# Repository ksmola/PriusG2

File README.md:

# Prius G2 Inverter controller

## About 

Inverter control board for Toyota Prius Gen 2 (XW20) inverter. 
Some of the schematics are based on Johannes Huebner's work found [here](https://github.com/jsphuebner/inverter-hardware).
Running [openinverter](http://www.openinverter.org) firmware.

    - ESP32 on board
    - AMPSEAL connectors
    - 3D printed enclosure

## Prerequisites 

ESP32 needs [ported webinterface](https://github.com/Bedz01/esp32-web-interface-port)
Get latest openinverter firmware [here](https://github.com/jsphuebner/stm32-sine/releases)

## Pinout 

Pinout is documented on the bottom silk of the PCB

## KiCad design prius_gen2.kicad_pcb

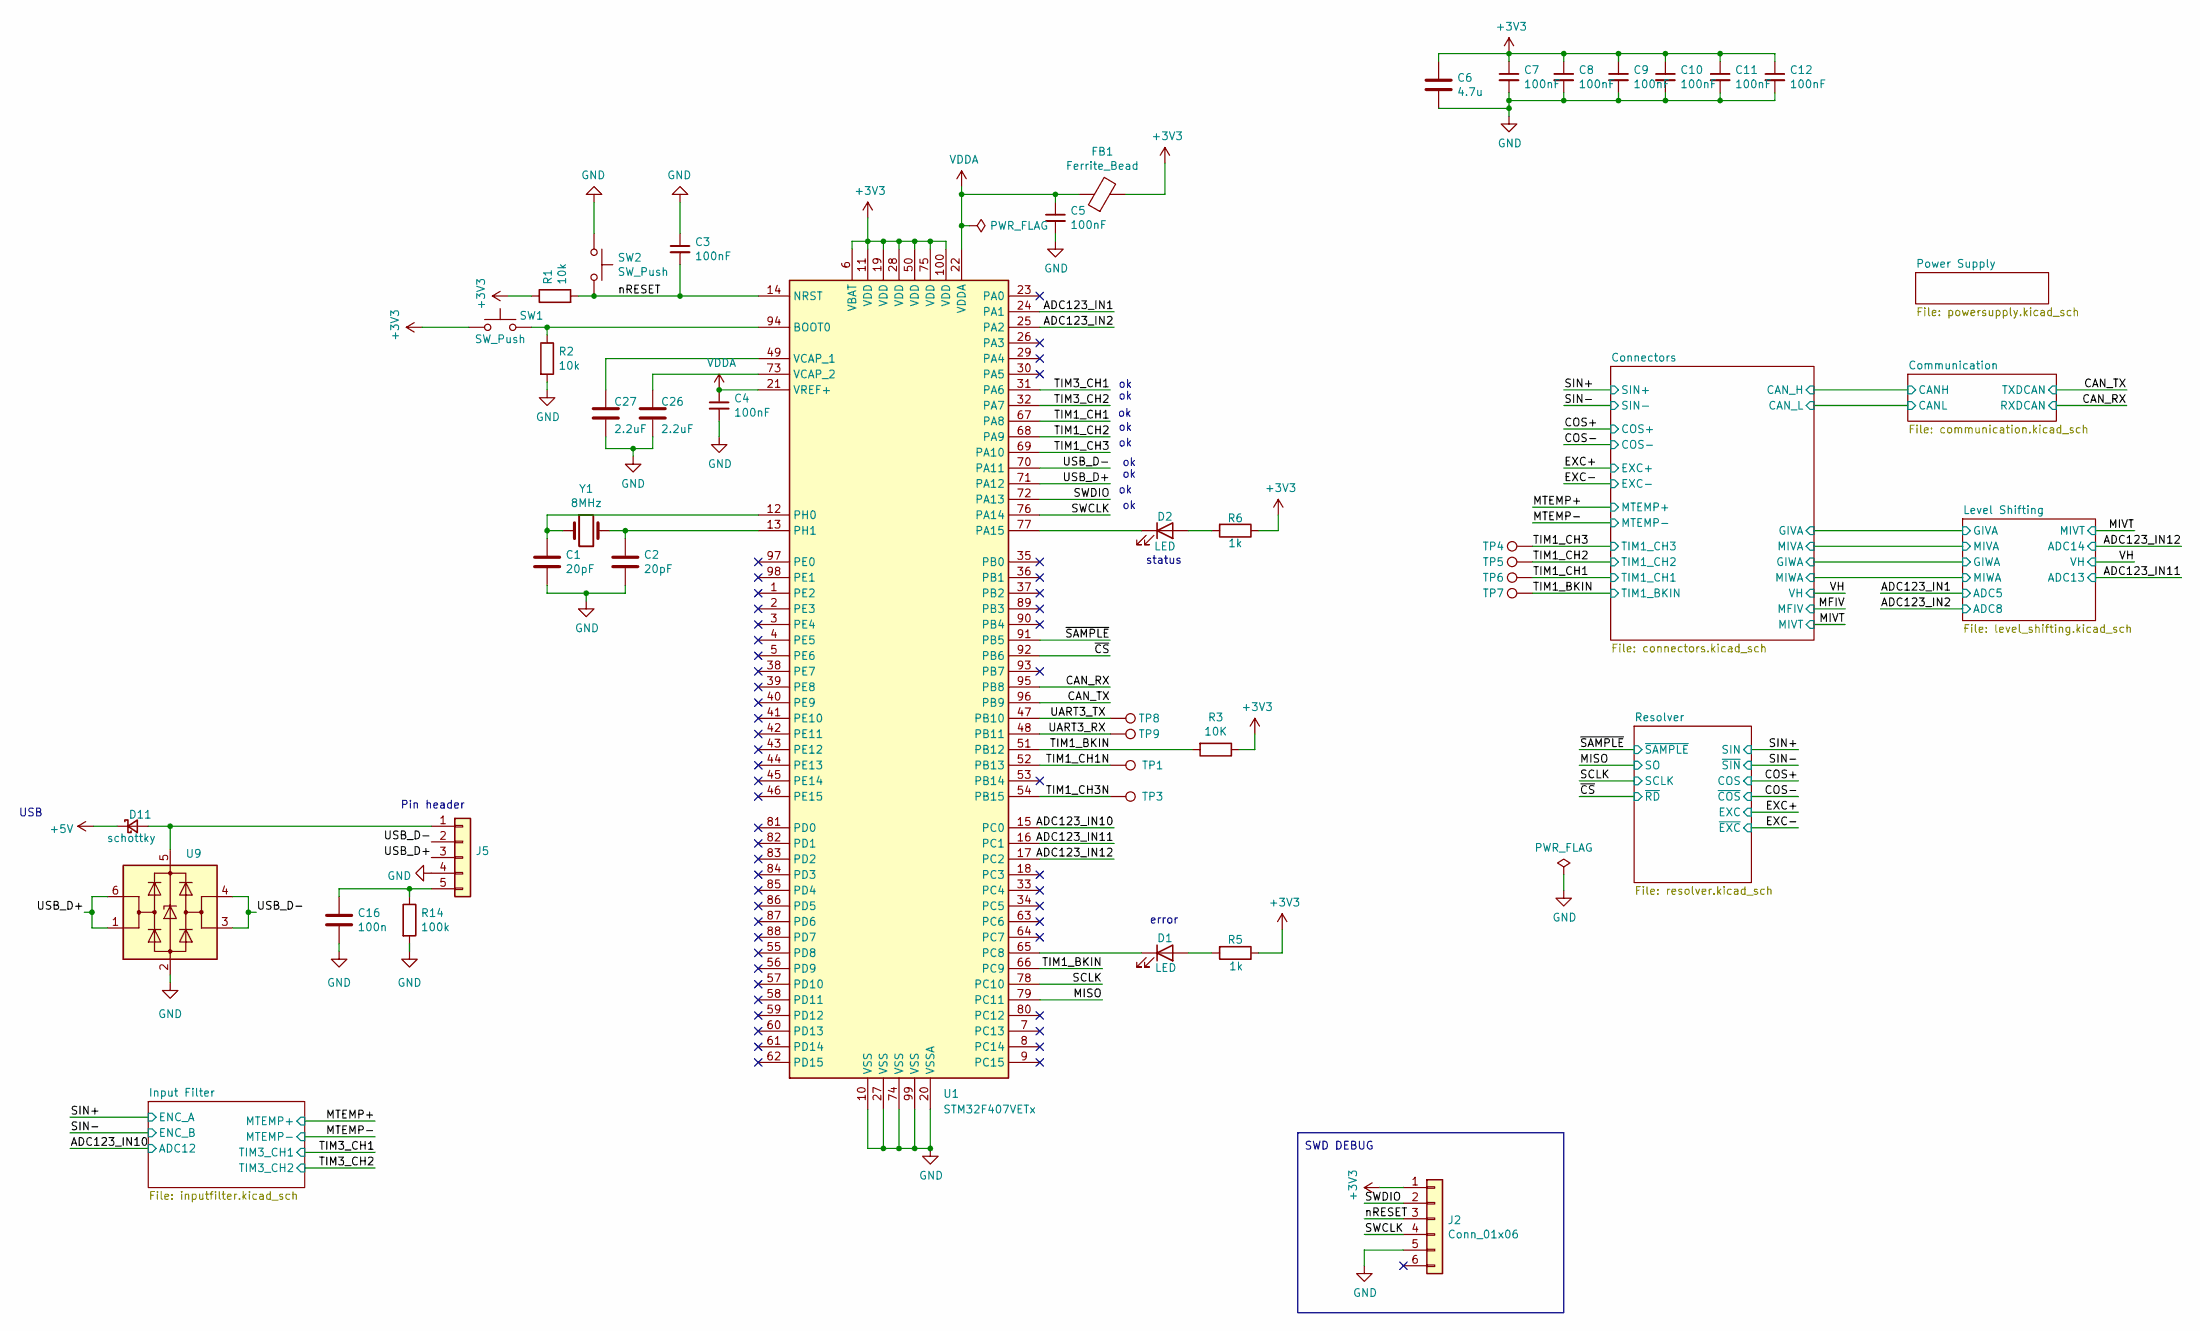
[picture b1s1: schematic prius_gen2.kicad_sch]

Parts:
C1, C2: 20pF; C_0603_1608Metric; mpn CC0603JRNPO9BN200; LCSC C105621
C3, C4, C5, C7, C8, C9, C10, C11, C12: 100nF; C_0603_1608Metric
C6: 4.7u; C_0603_1608Metric
C16: 100n; C_0603_1608Metric; LCSC C14663
C26, C27: 2.2uF; C_0603_1608Metric; LCSC C23630
D1, D2: LED; LED_0603_1608Metric_Castellated
D11: schottky; D_SOD-123; LCSC C8598
FB1: Ferrite_Bead; C_0805_2012Metric
J2: Conn_01x06; Tag-Connect_TC2030-IDC-NL_2x03_P1.27mm_Vertical
J5: PinSocket_1x05_P2.54mm_Vertical; LCSC N/A
R1, R2: 10k; R_0603_1608Metric; LCSC C25804
R3: 10K; R_0603_1608Metric; LCSC C25804
R5, R6: 1k; R_0603_1608Metric
R14: 100k; R_0402_1005Metric; LCSC C25741
SW1, SW2: SW_Push; SW_SPST_EVQQ2
TP1, TP3, TP4, TP5, TP6, TP7, TP8, TP9: TestPoint; TestPoint_Keystone_5000-5004_Miniature; LCSC C238124
U1: STM32F407VETx; LQFP-100_14x14mm_P0.5mm
U9: SOT-23-6; LCSC C7519
Y1: 8MHz; Crystal_SMD_5032-2Pin_5.0x3.2mm; LCSC C115962

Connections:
+3V3: C6.1, C7.1, C8.1, C9.1, C10.1, C11.1, C12.1, FB1.2, J2.1, R1.1, R3.1, R5.1, R6.1, SW1.1, U1.6 (VBAT), U1.11 (VDD), U1.19 (VDD), U1.28 (VDD), U1.50 (VDD), U1.75 (VDD), U1.100 (VDD); also elsewhere on the board
+5V: D11.1 (K); also elsewhere on the board
/ADC123_IN1: U1.24 (PA1); also elsewhere on the board
/ADC123_IN2: U1.25 (PA2); also elsewhere on the board
/ADC123_IN10: U1.15 (PC0); also elsewhere on the board
/ADC123_IN11: U1.16 (PC1); also elsewhere on the board
/ADC123_IN12: U1.17 (PC2); also elsewhere on the board
/CAN_RX: U1.95 (PB8); also elsewhere on the board
/CAN_TX: U1.96 (PB9); also elsewhere on the board
/MISO: U1.79 (PC11); also elsewhere on the board
/SCLK: U1.78 (PC10); also elsewhere on the board
/SWCLK: J2.4, U1.76 (PA14)
/SWDIO: J2.2, U1.72 (PA13)
/TIM1_BKIN: R3.2, TP7.1, U1.51 (PB12), U1.66 (PC9); also elsewhere on the board
/TIM1_CH1: TP6.1, U1.67 (PA8); also elsewhere on the board
/TIM1_CH1N: TP1.1, U1.52 (PB13)
/TIM1_CH2: TP5.1, U1.68 (PA9); also elsewhere on the board
/TIM1_CH3: TP4.1, U1.69 (PA10); also elsewhere on the board
/TIM1_CH3N: TP3.1, U1.54 (PB15)
/TIM3_CH1: U1.31 (PA6); also elsewhere on the board
/TIM3_CH2: U1.32 (PA7); also elsewhere on the board
/UART3_RX: TP9.1, U1.48 (PB11)
/UART3_TX: TP8.1, U1.47 (PB10)
/USB_D+: J5.3, U1.71 (PA12), U9.1 (I/O1), U9.6 (I/O1)
/USB_D-: J5.2, U1.70 (PA11), U9.3 (I/O2), U9.4 (I/O2)
/nRESET: C3.2, J2.3, R1.2, SW2.2, U1.14 (NRST)
/~CS: U1.92 (PB6); also elsewhere on the board
/~SAMPLE: U1.91 (PB5); also elsewhere on the board
GND: C1.1, C2.1, C3.1, C4.2, C5.2, C6.2, C7.2, C8.2, C9.2, C10.2, C11.2, C12.2, C16.2, C26.2, C27.2, J2.5, J5.4, R2.2, R14.2, SW2.1, U1.10 (VSS), U1.20 (VSSA), U1.27 (VSS), U1.74 (VSS), U1.99 (VSS), U9.2 (GND); also elsewhere on the board
unnamed: D1.2 (A), R5.2
unnamed: D1.1 (K), U1.65 (PC8)
unnamed: D2.2 (A), R6.2
unnamed: D2.1 (K), U1.77 (PA15)
unnamed: D11.2 (A), J5.1, U9.5 (VBUS)
unnamed: C16.1, J5.5, R14.1
unnamed: R2.1, SW1.2, U1.94 (BOOT0)
unnamed: C1.2, U1.12 (PH0), Y1.1
unnamed: C2.2, U1.13 (PH1), Y1.2
unnamed: C27.1, U1.49 (VCAP_1)
unnamed: C26.1, U1.73 (VCAP_2)
VDDA: C4.1, C5.1, FB1.1, U1.21 (VREF+), U1.22 (VDDA)

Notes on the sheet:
USB
status
SWD DEBUG
Pin header
error

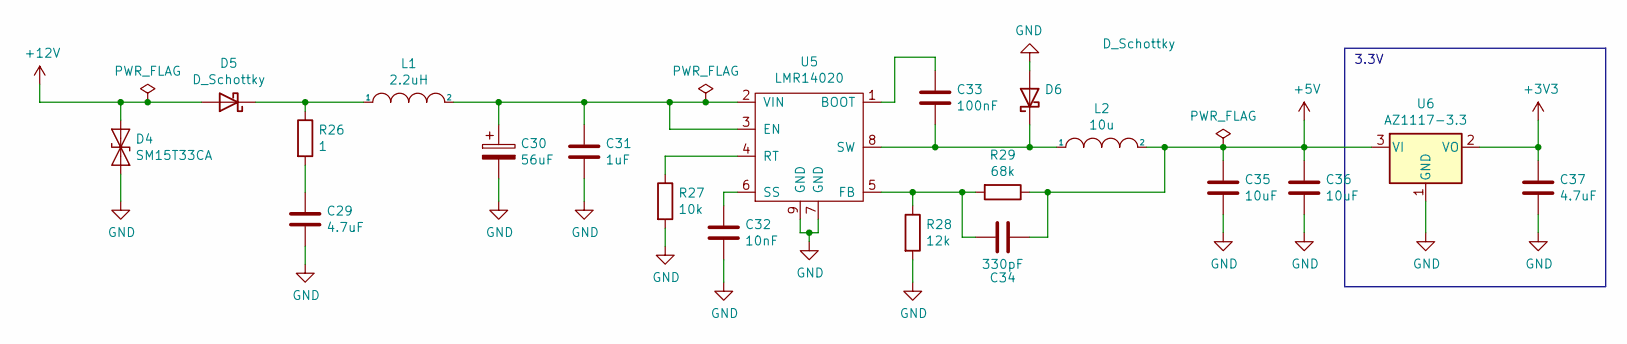
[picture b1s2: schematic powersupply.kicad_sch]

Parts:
C29, C37: 4.7uF; C_0603_1608Metric
C30: 56uF; CP_Radial_D8.0mm_P3.50mm
C31: 1uF; C_0603_1608Metric
C32: 10nF; C_0603_1608Metric; LCSC C302008
C33: 100nF; C_0603_1608Metric
C34: 330pF; C_0603_1608Metric
C35, C36: 10uF; C_0603_1608Metric
D4: SM15T33CA; D_SMC
D5, D6: D_Schottky; D_SMA
L1: 2.2uH; L_1210_3225Metric
L2: 10u; MWSA0503
R26: 1; R_0603_1608Metric
R27: 10k; R_0603_1608Metric; LCSC C25804
R28: 12k; R_0603_1608Metric
R29: 68k; R_0603_1608Metric; LCSC C23231
U5: LMR14020; SOIC-8-1EP_3.9x4.9mm_P1.27mm_EP2.29x3mm
U6: AZ1117-3.3; SOT-223-3_TabPin2

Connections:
+3V3: C37.1, U6.2 (VO); also elsewhere on the board
+5V: C34.2, C35.1, C36.1, L2.2, R29.1, U6.3 (VI); also elsewhere on the board
+12V: D4.1 (A1), D5.2 (A); also elsewhere on the board
GND: C29.2, C30.2, C31.2, C32.2, C35.2, C36.2, C37.2, D4.2 (A2), D6.2 (A), R27.2, R28.2, U5.7 (GND), U5.9 (GND), U6.1 (GND); also elsewhere on the board
unnamed: C29.1, R26.2
unnamed: D5.1 (K), L1.1, R26.1
unnamed: C33.2, D6.1 (K), L2.1, U5.8 (SW)
unnamed: C33.1, U5.1 (BOOT)
unnamed: C30.1, C31.1, L1.2, U5.2 (VIN), U5.3 (EN)
unnamed: C34.1, R28.1, R29.2, U5.5 (FB)
unnamed: R27.1, U5.4 (RT)
unnamed: C32.1, U5.6 (SS)

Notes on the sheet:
3.3V

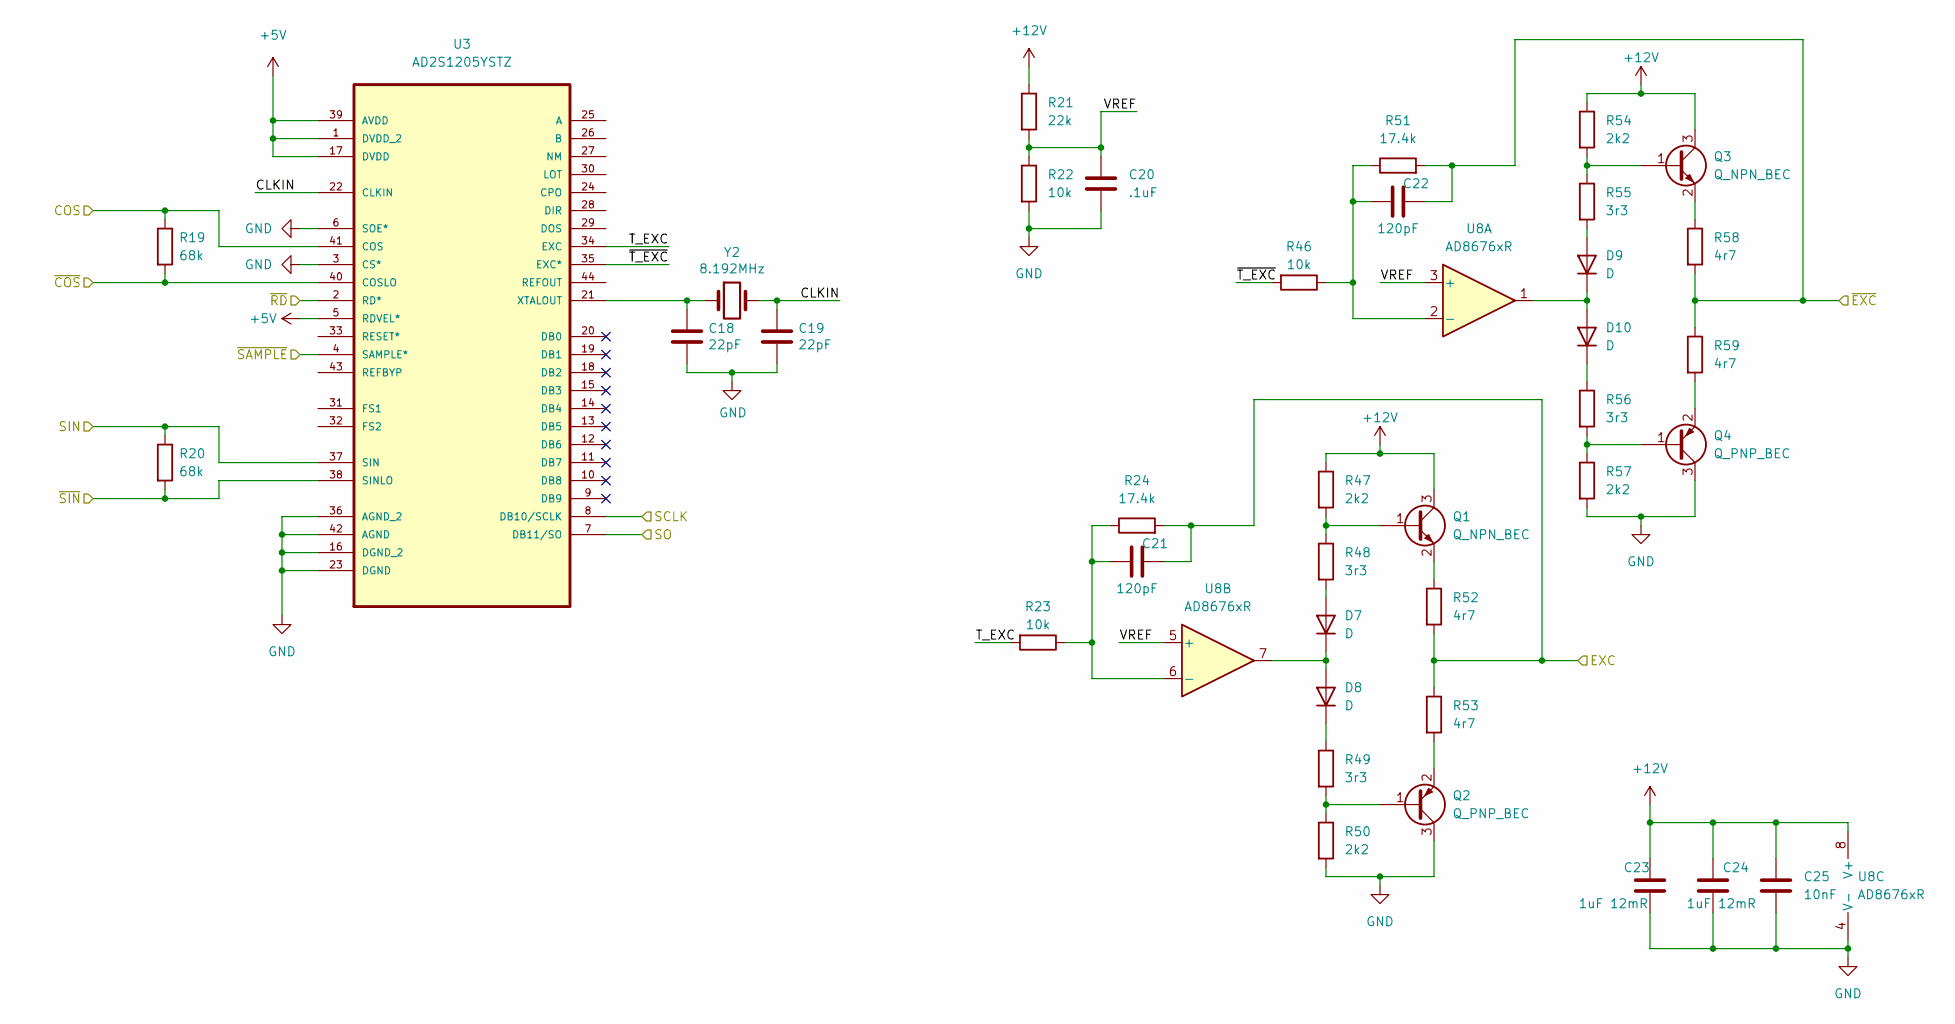
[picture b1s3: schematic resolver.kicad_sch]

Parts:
C18, C19: 22pF; C_0603_1608Metric; mpn CC0603JRNPO9BN200; LCSC C309441
C20: .1uF; C_0603_1608Metric; LCSC C15725
C21, C22: 120pF; C_0603_1608Metric; LCSC C1643
C23, C24: 1uF 12mR; C_0603_1608Metric; LCSC C106858
C25: 10nF; C_0603_1608Metric; LCSC C302008
D7, D8, D9, D10: D; D_SOD-123; LCSC C83528
Q1, Q3: Q_NPN_BEC; TSOT-23; LCSC C2144
Q2, Q4: Q_PNP_BEC; TSOT-23; LCSC C8326
R19, R20: 68k; R_0603_1608Metric; LCSC C23231
R21: 22k; R_0603_1608Metric
R22, R23, R46: 10k; R_0603_1608Metric; LCSC C25804
R24, R51: 17.4k; R_0603_1608Metric; LCSC C269466
R47, R50, R54, R57: 2k2; R_0603_1608Metric; LCSC C325643
R48, R49, R55, R56: 3r3; R_0603_1608Metric; LCSC C365471
R52, R53, R58, R59: 4r7; R_0603_1608Metric; LCSC C23164
U3: AD2S1205YSTZ; QFP80P1200X1200X160-44N; MPN AD2S1205YSTZ; LCSC C91729
U8: AD8676xR; SOIC-8_3.9x4.9mm_P1.27mm; LCSC C28133
Y2: 8.192MHz; Crystal_SMD_5032-2Pin_5.0x3.2mm; LCSC C115962

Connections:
+5V: U3.1 (DVDD_2), U3.5 (RDVEL*), U3.17 (DVDD), U3.39 (AVDD); also elsewhere on the board
+12V: C23.1, C24.1, C25.1, Q1.3 (C), Q3.3 (C), R21.1, R47.1, R54.1, U8.8 (V+); also elsewhere on the board
/COS+: R19.1, U3.41 (COS); also elsewhere on the board
/COS-: R19.2, U3.40 (COSLO); also elsewhere on the board
/EXC+: C21.2, R24.2, R52.2, R53.1; also elsewhere on the board
/EXC-: C22.2, R51.2, R58.2, R59.1; also elsewhere on the board
/MISO: U3.7 (DB11/SO); also elsewhere on the board
/Resolver/CLKIN: C19.2, U3.22 (CLKIN), Y2.2
/Resolver/T_EXC: R23.2, U3.34 (EXC)
/Resolver/VREF: C20.1, R21.2, R22.1, U8.3 (+), U8.5 (+)
/Resolver/~T_EXC: R46.2, U3.35 (EXC*)
/SCLK: U3.8 (DB10/SCLK); also elsewhere on the board
/SIN+: R20.1, U3.37 (SIN); also elsewhere on the board
/SIN-: R20.2, U3.38 (SINLO); also elsewhere on the board
/~CS: U3.2 (RD*); also elsewhere on the board
/~SAMPLE: U3.4 (SAMPLE*); also elsewhere on the board
GND: C18.1, C19.1, C20.2, C23.2, C24.2, C25.2, Q2.3 (C), Q4.3 (C), R22.2, R50.2, R57.2, U3.3 (CS*), U3.6 (SOE*), U3.16 (DGND_2), U3.23 (DGND), U3.36 (AGND_2), U3.42 (AGND), U8.4 (V-); also elsewhere on the board
unnamed: D7.2 (A), R48.2
unnamed: D7.1 (K), D8.2 (A), U8.7
unnamed: D8.1 (K), R49.1
unnamed: D9.2 (A), R55.2
unnamed: D9.1 (K), D10.2 (A), U8.1
unnamed: D10.1 (K), R56.1
unnamed: Q1.1 (B), R47.2, R48.1
unnamed: Q1.2 (E), R52.1
unnamed: Q2.1 (B), R49.2, R50.1
unnamed: Q2.2 (E), R53.2
unnamed: Q3.1 (B), R54.2, R55.1
unnamed: Q3.2 (E), R58.1
unnamed: Q4.1 (B), R56.2, R57.1
unnamed: Q4.2 (E), R59.2
unnamed: C18.2, U3.21 (XTALOUT), Y2.1
unnamed: C22.1, R46.1, R51.1, U8.2 (-)
unnamed: C21.1, R23.1, R24.1, U8.6 (-)

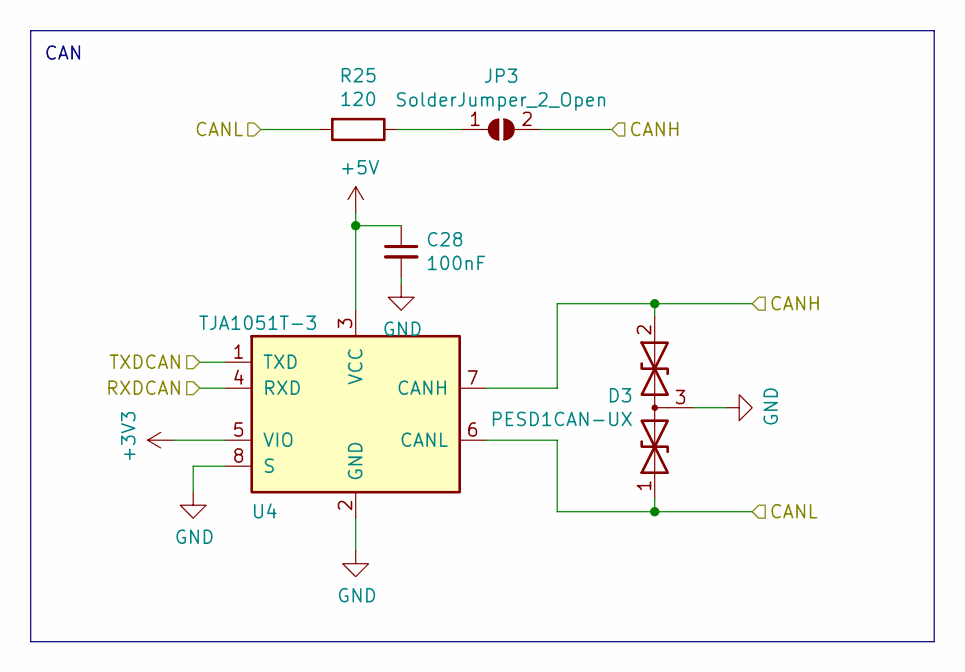
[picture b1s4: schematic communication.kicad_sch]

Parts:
C28: 100nF; C_0603_1608Metric
D3: PESD1CAN-UX; SOT-323_SC-70
JP3: SolderJumper_2_Open; SolderJumper-2_P1.3mm_Open_TrianglePad1.0x1.5mm
R25: 120; R_0603_1608Metric
U4: TJA1051T-3; SOIC-8_3.9x4.9mm_P1.27mm

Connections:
+3V3: U4.5 (VIO); also elsewhere on the board
+5V: C28.1, U4.3 (VCC); also elsewhere on the board
/CAN_RX: U4.4 (RXD); also elsewhere on the board
/CAN_TX: U4.1 (TXD); also elsewhere on the board
/Communication/CANH: D3.2 (A2), JP3.2 (B), U4.7 (CANH); also elsewhere on the board
/Communication/CANL: D3.1 (A1), R25.2, U4.6 (CANL); also elsewhere on the board
GND: C28.2, D3.3 (common), U4.2 (GND), U4.8 (S); also elsewhere on the board
unnamed: JP3.1 (A), R25.1

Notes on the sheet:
CAN

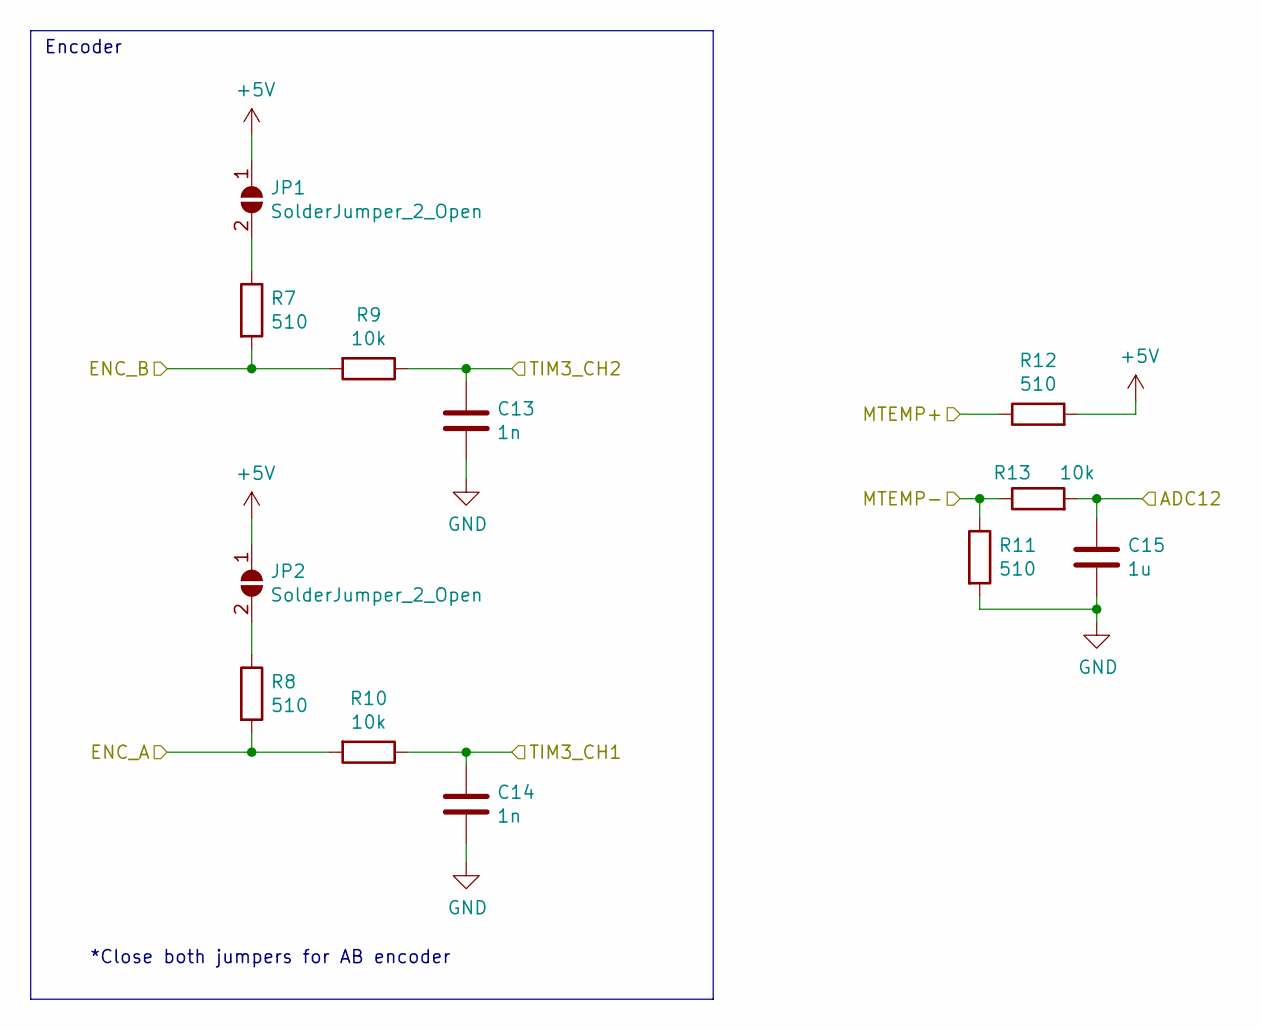
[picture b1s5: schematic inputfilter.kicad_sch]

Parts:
C13, C14: 1n; C_0603_1608Metric
C15: 1u; C_0603_1608Metric
JP1, JP2: SolderJumper_2_Open; SolderJumper-2_P1.3mm_Open_TrianglePad1.0x1.5mm
R7, R8, R11, R12: 510; R_0603_1608Metric
R9, R10, R13: 10k; R_0603_1608Metric; LCSC C25804

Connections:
+5V: JP1.1 (A), JP2.1 (A), R12.2; also elsewhere on the board
/ADC123_IN10: C15.1, R13.2; also elsewhere on the board
/MTEMP+: R12.1; also elsewhere on the board
/MTEMP-: R11.1, R13.1; also elsewhere on the board
/SIN+: R8.2, R10.2; also elsewhere on the board
/SIN-: R7.2, R9.2; also elsewhere on the board
/TIM3_CH1: C14.1, R10.1; also elsewhere on the board
/TIM3_CH2: C13.1, R9.1; also elsewhere on the board
GND: C13.2, C14.2, C15.2, R11.2; also elsewhere on the board
unnamed: JP1.2 (B), R7.1
unnamed: JP2.2 (B), R8.1

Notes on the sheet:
*Close both jumpers for AB encoder
Encoder

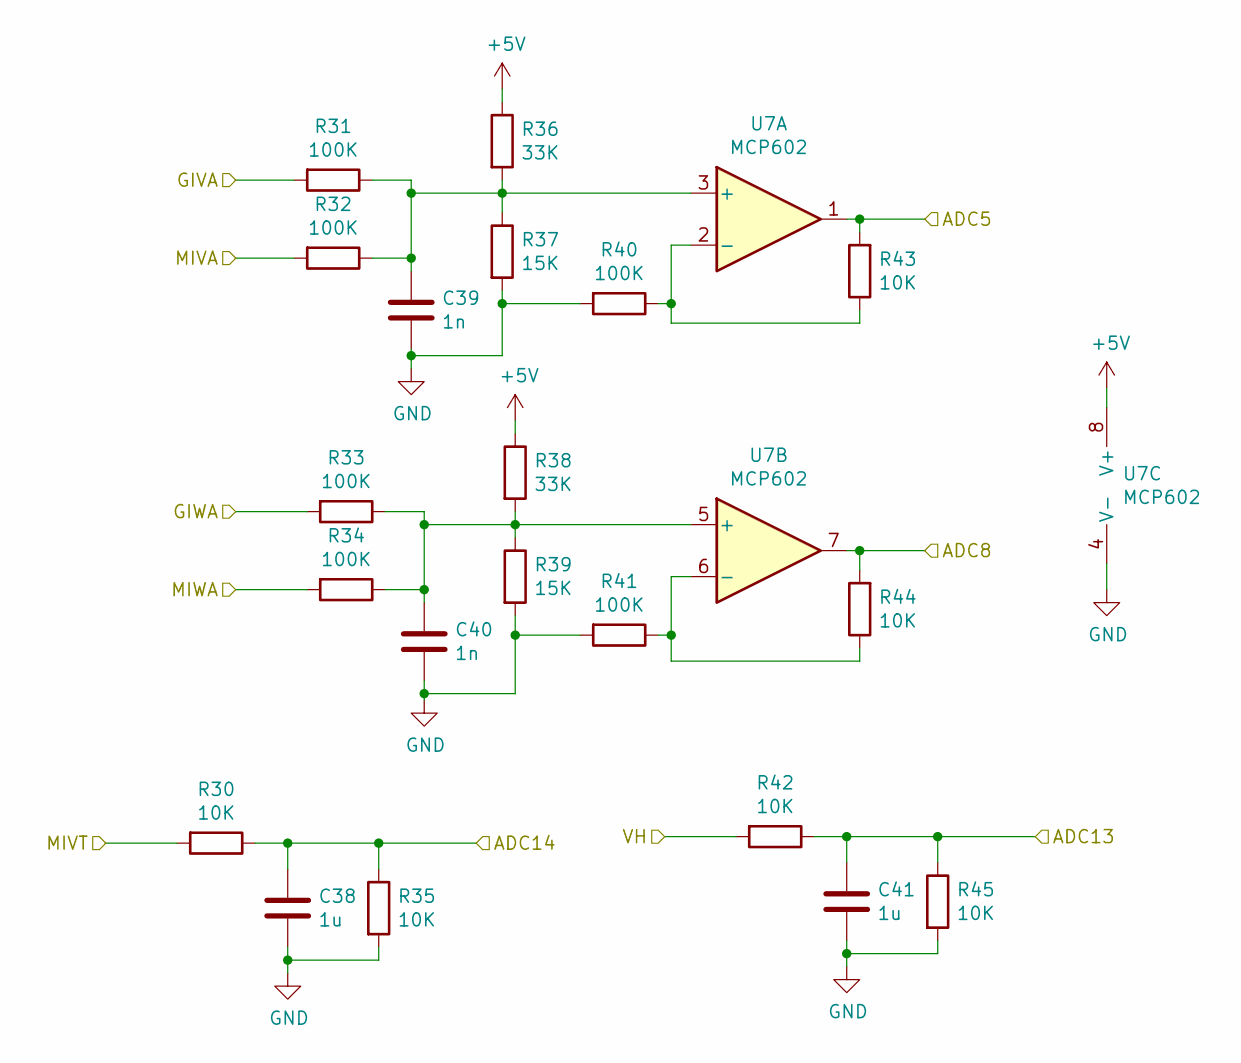
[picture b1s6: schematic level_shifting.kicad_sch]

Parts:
C38, C41: 1u; C_0603_1608Metric
C39, C40: 1n; C_0603_1608Metric
R30, R35, R42, R45: 10K; R_0603_1608Metric; LCSC C25804
R31, R32, R33, R34, R40, R41: 100K; R_0603_1608Metric
R36, R38: 33K; R_0603_1608Metric
R37, R39: 15K; R_0603_1608Metric
R43, R44: 10K; R_0603_1608Metric
U7: MCP602; SOIC-8-1EP_3.9x4.9mm_P1.27mm_EP2.29x3mm

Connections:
+5V: R36.1, R38.1, U7.8 (V+); also elsewhere on the board
/ADC123_IN1: R43.2, U7.1; also elsewhere on the board
/ADC123_IN2: R44.2, U7.7; also elsewhere on the board
/ADC123_IN11: C41.1, R42.1, R45.1; also elsewhere on the board
/ADC123_IN12: C38.1, R30.1, R35.1; also elsewhere on the board
/Connectors/GIVA: R31.2; also elsewhere on the board
/Connectors/GIWA: R33.2; also elsewhere on the board
/Connectors/MIVA: R32.2; also elsewhere on the board
/Connectors/MIWA: R34.2; also elsewhere on the board
/MIVT: R30.2; also elsewhere on the board
/VH: R42.2; also elsewhere on the board
GND: C38.2, C39.2, C40.2, C41.2, R35.2, R37.2, R39.2, R40.2, R41.2, R45.2, U7.4 (V-); also elsewhere on the board
unnamed: C39.1, R31.1, R32.1, R36.2, R37.1, U7.3 (+)
unnamed: R40.1, R43.1, U7.2 (-)
unnamed: C40.1, R33.1, R34.1, R38.2, R39.1, U7.5 (+)
unnamed: R41.1, R44.1, U7.6 (-)

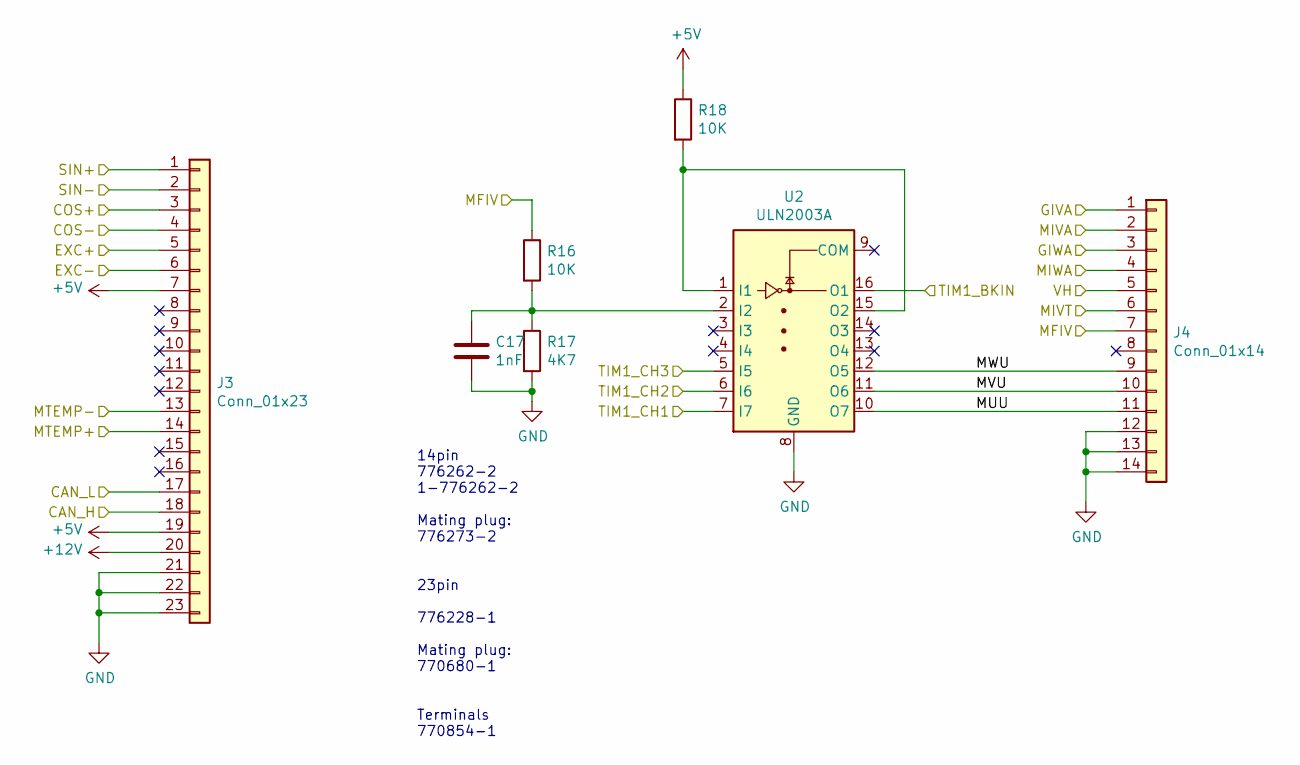
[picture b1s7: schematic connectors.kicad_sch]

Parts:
C17: 1nF; C_0603_1608Metric
J3: Conn_01x23; TE_776228-1
J4: Conn_01x14; TE_776262-2
R16, R18: 10K; R_0603_1608Metric; LCSC C25804
R17: 4K7; R_0603_1608Metric
U2: ULN2003A; SOIC-16_4.55x10.3mm_P1.27mm

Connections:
+5V: J3.7, J3.19, R18.1; also elsewhere on the board
+12V: J3.20; also elsewhere on the board
/COS+: J3.3; also elsewhere on the board
/COS-: J3.4; also elsewhere on the board
/Communication/CANH: J3.18; also elsewhere on the board
/Communication/CANL: J3.17; also elsewhere on the board
/Connectors/GIVA: J4.1; also elsewhere on the board
/Connectors/GIWA: J4.3; also elsewhere on the board
/Connectors/MIVA: J4.2; also elsewhere on the board
/Connectors/MIWA: J4.4; also elsewhere on the board
/Connectors/MUU: J4.11, U2.10 (O7)
/Connectors/MVU: J4.10, U2.11 (O6)
/Connectors/MWU: J4.9, U2.12 (O5)
/EXC+: J3.5; also elsewhere on the board
/EXC-: J3.6; also elsewhere on the board
/MFIV: J4.7, R16.1
/MIVT: J4.6; also elsewhere on the board
/MTEMP+: J3.14; also elsewhere on the board
/MTEMP-: J3.13; also elsewhere on the board
/SIN+: J3.1; also elsewhere on the board
/SIN-: J3.2; also elsewhere on the board
/TIM1_BKIN: U2.16 (O1); also elsewhere on the board
/TIM1_CH1: U2.7 (I7); also elsewhere on the board
/TIM1_CH2: U2.6 (I6); also elsewhere on the board
/TIM1_CH3: U2.5 (I5); also elsewhere on the board
/VH: J4.5; also elsewhere on the board
GND: C17.2, J3.21, J3.22, J3.23, J4.12, J4.13, J4.14, R17.2, U2.8 (GND); also elsewhere on the board
unnamed: R18.2, U2.1 (I1), U2.15 (O2)
unnamed: C17.1, R16.2, R17.1, U2.2 (I2)

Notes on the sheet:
14pin 776262-2 1-776262-2 Mating plug: 776273-2 23pin 776228-1 Mating plug: 770680-1 Terminals 770854-1

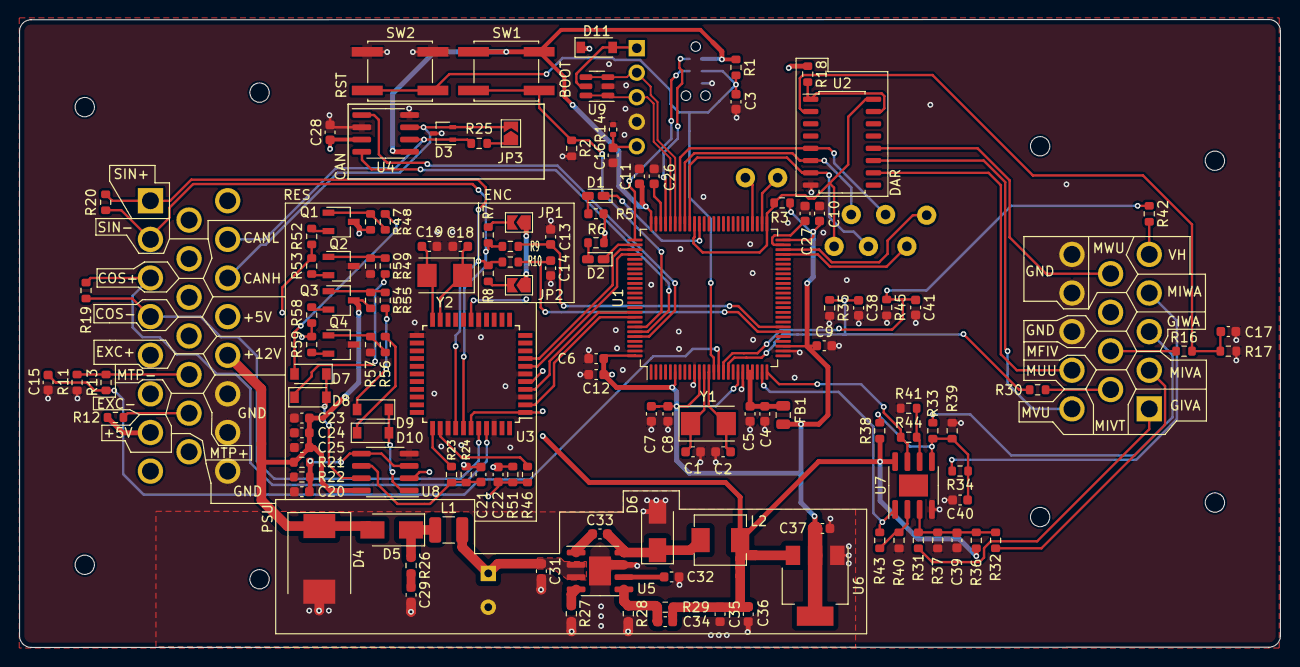
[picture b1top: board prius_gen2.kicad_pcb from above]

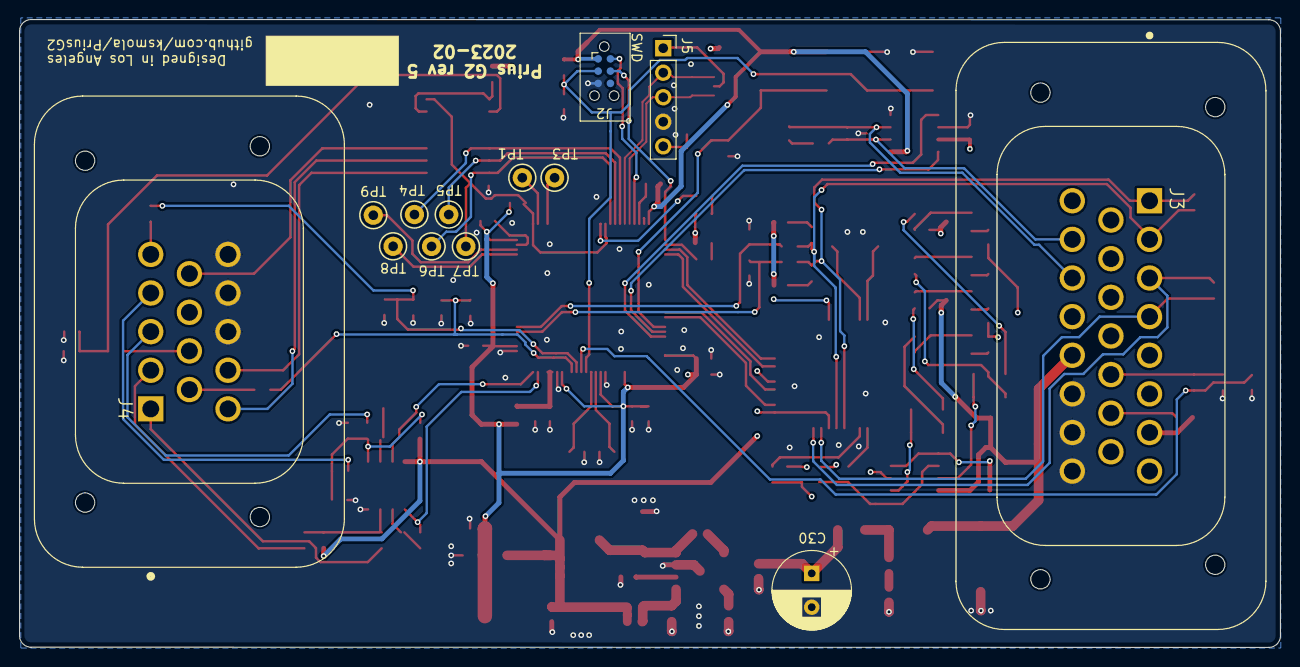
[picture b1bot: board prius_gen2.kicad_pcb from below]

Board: 4 copper layers, 130.6 x 65.0 mm, 144 parts (13 on the bottom side), 100 nets.

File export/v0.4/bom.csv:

Designator,Footprint,Quantity,Value,LCSC Part #
R13,R_0603_1608Metric,1,10k,C25804
C29,C_0603_1608Metric,1,4.7uF,
C31,C_0603_1608Metric,1,1uF,
C32,C_0603_1608Metric,1,10nF,C302008
C33,C_0603_1608Metric,1,100nF,
C34,C_0603_1608Metric,1,330pF,
R29,R_0603_1608Metric,1,68k,C23231
R7,R_0603_1608Metric,1,510,
R42,R_0603_1608Metric,1,10K,C25804
R28,R_0603_1608Metric,1,12k,
C35,C_0603_1608Metric,1,10uF,
C36,C_0603_1608Metric,1,10uF,
C37,C_0603_1608Metric,1,4.7uF,
C13,C_0603_1608Metric,1,1n,
C14,C_0603_1608Metric,1,1n,
C15,C_0603_1608Metric,1,1u,
SW1,SW_SPST_EVQQ2,1,SW_Push,
U4,SOIC-8_3.9x4.9mm_P1.27mm,1,TJA1051T-3,
C6,C_0603_1608Metric,1,4.7u,
C38,C_0603_1608Metric,1,1u,
C41,C_0603_1608Metric,1,1u,
R11,R_0603_1608Metric,1,510,
R12,R_0603_1608Metric,1,510,
R10,R_0603_1608Metric,1,10k,C25804
R25,R_0603_1608Metric,1,120,
R26,R_0603_1608Metric,1,1,
Y1,Crystal_SMD_5032-2Pin_5.0x3.2mm,1,8MHz,C115962
SW2,SW_SPST_EVQQ2,1,SW_Push,
D2,LED_0603_1608Metric_Castellated,1,LED,
R8,R_0603_1608Metric,1,510,
R9,R_0603_1608Metric,1,10k,C25804
R35,R_0603_1608Metric,1,10K,C25804
R4,R_0603_1608Metric,1,10K,C25804
R30,R_0603_1608Metric,1,10K,C25804
JP2,SolderJumper-2_P1.3mm_Open_TrianglePad1.0x1.5mm,1,SolderJumper_2_Open,
L1,L_1210_3225Metric,1,2.2uH,
R1,R_0603_1608Metric,1,10k,C25804
D3,SOT-323_SC-70,1,PESD1CAN-UX,
D4,D_SMC,1,SM15T33CA,
D5,D_SMA,1,D_Schottky,
D6,D_SMA,1,D_Schottky,
FB1,C_0805_2012Metric,1,Ferrite_Bead,
R45,R_0603_1608Metric,1,10K,C25804
R27,R_0603_1608Metric,1,10k,C25804
R6,R_0603_1608Metric,1,1k,
R2,R_0603_1608Metric,1,10k,C25804
JP3,SolderJumper-2_P1.3mm_Open_TrianglePad1.0x1.5mm,1,SolderJumper_2_Open,
JP1,SolderJumper-2_P1.3mm_Open_TrianglePad1.0x1.5mm,1,SolderJumper_2_Open,
U6,SOT-223-3_TabPin2,1,AZ1117-3.3,
U5,SOIC-8-1EP_3.9x4.9mm_P1.27mm_EP2.29x3mm,1,LMR14020,
R18,R_0603_1608Metric,1,10K,C25804
C17,C_0603_1608Metric,1,1nF,
R16,R_0603_1608Metric,1,10K,C25804
R17,R_0603_1608Metric,1,4K7,
U7,SOIC-8-1EP_3.9x4.9mm_P1.27mm_EP2.29x3mm,1,MCP602,
R41,R_0603_1608Metric,1,100K,
C39,C_0603_1608Metric,1,1n,
C40,C_0603_1608Metric,1,1n,
R43,R_0603_1608Metric,1,10K,
R34,R_0603_1608Metric,1,100K,
R38,R_0603_1608Metric,1,33K,
R36,R_0603_1608Metric,1,33K,
R37,R_0603_1608Metric,1,15K,
R33,R_0603_1608Metric,1,100K,
R31,R_0603_1608Metric,1,100K,
R32,R_0603_1608Metric,1,100K,
R39,R_0603_1608Metric,1,15K,
R40,R_0603_1608Metric,1,100K,
R44,R_0603_1608Metric,1,10K,
L2,MWSA0503,1,10u,
C2,C_0603_1608Metric,1,20pF,CC0603JRNPO9BN200
C7,C_0603_1608Metric,1,100nF,
C4,C_0603_1608Metric,1,100nF,
C8,C_0603_1608Metric,1,100nF,
C9,C_0603_1608Metric,1,100nF,
C11,C_0603_1608Metric,1,100nF,
C12,C_0603_1608Metric,1,100nF,
C3,C_0603_1608Metric,1,100nF,
C5,C_0603_1608Metric,1,100nF,
C28,C_0603_1608Metric,1,100nF,
C1,C_0603_1608Metric,1,20pF,CC0603JRNPO9BN200
R5,R_0603_1608Metric,1,1k,
D1,LED_0603_1608Metric_Castellated,1,LED,
R3,R_0603_1608Metric,1,10K,C25804
C10,C_0603_1608Metric,1,100nF,
U2,SOIC-16_4.55x10.3mm_P1.27mm,1,ULN2003A,
R54,R_0603_1608Metric,1,2k2,C325643
J5,PinSocket_1x05_P2.54mm_Vertical,1,~,N/A
D9,D_SOD-123,1,D,C83528
U9,SOT-23-6,1,~,C7519
R23,R_0603_1608Metric,1,10k,C25804
C21,C_0603_1608Metric,1,120pF,C1643
R24,R_0603_1608Metric,1,17.4k,C269466
R47,R_0603_1608Metric,1,2k2,C325643
D8,D_SOD-123,1,D,C83528
C25,C_0603_1608Metric,1,10nF,C302008
Q3,TSOT-23,1,Q_NPN_BEC,C2144
C23,C_0603_1608Metric,1,1uF 12mR,C106858
Q4,TSOT-23,1,Q_PNP_BEC,C8326
R51,R_0603_1608Metric,1,17.4k,C269466
R57,R_0603_1608Metric,1,2k2,C325643
D11,D_SOD-123,1,schottky,C8598
R56,R_0603_1608Metric,1,3r3,C365471
U1,LQFP-100_14x14mm_P0.5mm,1,STM32F407VETx,
R22,R_0603_1608Metric,1,10k,C25804
R53,R_0603_1608Metric,1,4r7,C23164
D7,D_SOD-123,1,D,C83528
U3,QFP80P1200X1200X160-44N,1,AD2S1205YSTZ,AD2S1205YSTZ
R49,R_0603_1608Metric,1,3r3,C365471
C20,C_0603_1608Metric,1,.1uF,C15725
R55,R_0603_1608Metric,1,3r3,C365471
R20,R_0603_1608Metric,1,68k,C23231
R50,R_0603_1608Metric,1,2k2,C325643
R21,R_0603_1608Metric,1,22k,
C24,C_0603_1608Metric,1,1uF 12mR,C106858
R59,R_0603_1608Metric,1,4r7,C23164
R52,R_0603_1608Metric,1,4r7,C23164
C18,C_0603_1608Metric,1,22pF,CC0603JRNPO9BN200
R48,R_0603_1608Metric,1,3r3,C365471
C22,C_0603_1608Metric,1,120pF,C1643
R19,R_0603_1608Metric,1,68k,C23231
Q1,TSOT-23,1,Q_NPN_BEC,C2144
C16,C_0603_1608Metric,1,100n,C14663
R14,R_0402_1005Metric,1,100k,C25741
Q2,TSOT-23,1,Q_PNP_BEC,C8326
R46,R_0603_1608Metric,1,10k,C25804
U8,SOIC-8_3.9x4.9mm_P1.27mm,1,AD8676xR,
Y2,Crystal_SMD_5032-2Pin_5.0x3.2mm,1,8.192MHz,C115962
D10,D_SOD-123,1,D,C83528
C19,C_0603_1608Metric,1,22pF,CC0603JRNPO9BN200
R58,R_0603_1608Metric,1,4r7,C23164
C30,CP_Radial_D8.0mm_P3.50mm,1,56uF,
J3,TE_776228-1,1,Conn_01x23,
J2,Tag-Connect_TC2030-IDC-NL_2x03_P1.27mm_Vertical,1,Conn_01x06,
J4,TE_776262-2,1,Conn_01x14,
J1,PinHeader_2x05_P1.27mm_Vertical_SMD,1,Conn_02x05_Odd_Even,
TP6,TestPoint_Keystone_5000-5004_Miniature,1,TestPoint,C238124
TP3,TestPoint_Keystone_5000-5004_Miniature,1,TestPoint,C238124
TP4,TestPoint_Keystone_5000-5004_Miniature,1,TestPoint,C238124
TP7,TestPoint_Keystone_5000-5004_Miniature,1,TestPoint,C238124
TP2,TestPoint_Keystone_5000-5004_Miniature,1,TestPoint,C238124
TP1,TestPoint_Keystone_5000-5004_Miniature,1,TestPoint,C238124
TP5,TestPoint_Keystone_5000-5004_Miniature,1,TestPoint,C238124

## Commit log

2021-07-25 iniial commit...
2021-07-26 CAD case
2021-07-26 cleanup
2021-07-27 more cleanup
2021-07-28 added readme
2021-08-04 fixed schematics error
2021-08-04 updated routing
2021-08-04 more routing fixes
2021-08-05 updated silk and manuf. files
2021-08-05 fixed bom
2021-08-30 updated vals for 3stage RC filter
2021-09-03 more updates to RC filter; fixed pinout silk
2021-11-03 updated resolver schematics
2021-11-03 updates for release
2021-11-03 added case stl
2021-11-20 added pictures
2021-11-20 added image to readme
2022-12-24 updates for KiCAD 6
2022-12-26 started adding AD2S
2022-12-27 routed ad2s
2022-12-27 cleaned up board
2022-12-29 fixed resolver buffer circuit
2023-01-01 added USB
2023-01-01 v0.4 manufactoring files
2023-01-25 fixes for v5
2023-01-26 fixed some drc errors
2023-02-13 more updates for v0.5 prod
2023-02-14 fixed adcs
2023-02-15 v0.5 production files
